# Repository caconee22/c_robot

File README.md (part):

<div align="center">

# 🤖 C_ROBOT

### 2026 IRC 씨름 로봇 — 자율주행 스모 로봇 V2

**카메라로 상대를 찾고, 네 모서리 컬러 센서로 경기장 홈을 피하며, 포크로 상대를 밀어내는 4.5kg급 자율 로봇**

[-gold?style=for-the-badge)](IRC2026_RETROSPECTIVE.md)

[개요](#-개요) ·
[하드웨어](#-하드웨어) ·
[시스템 구조](#-시스템-구조) ·
[경기 펌웨어](#-경기-펌웨어) ·
[시작하기](#-시작하기) ·
[타임라인](#-타임라인) ·
[대회 데이터](#-대회-데이터) ·
[배운 것](#-배운-것) ·
[문서](#-문서-지도)

</div>

---

## 🏆 결과

> **2026-11-13, 2026 IRC 씨름 로봇 대회 1위 — 1점 차 우승.**
>
> 첫 설계부터 우승까지 42일. 모터 드라이버와 메인 보드가 타고, 회로를 처음부터 다시 만들고,
> 대회 당일 경기 중에 ESP32가 멈추는 문제를 현장에서 고쳐 가며 얻은 결과다.
> 우승 펌웨어는 태그 [`irc2026-final`](https://github.com/caconee22/c_robot/tree/irc2026-final)에 그대로 남아 있다.

| | |
|---|---|
| 📅 **기간** | 2026-10-03 → 2026-11-13 (42일), 정리 11/14 |
| 🧠 **제어** | ESP32-S3 단독 판단 · 루프 1~2ms · 모터 명령 80ms 만료 감시 |
| 👁️ **영상** | Raspberry Pi 5 + Camera Module 3 Wide · 720p 60fps · 좌표만 50Hz UART |
| 🎨 **바닥** | AS7341 스펙트럼 센서 ×4 · 12단계 교정 · 3/10/20mm 간격 변화 대응 |
| 📈 **기록** | 커밋 79 · PR 9 · 주행 로그 80개 · 분석 67판 61분 · AI 대화 27일 |

---

## 📖 개요

C_ROBOT은 **2026 IRC 씨름 로봇 대회**에 나간 자율주행 스모 로봇의 통합 저장소다.
펌웨어, 영상 처리, 회로·PCB, 기구, 팀 일정, 주행 로그, 그리고 개발 과정의 AI 대화까지 한곳에 있다.

경기 규칙의 핵심은 단순하다. 경기장 위에서 **상대 로봇(컬러 타워를 단)을 찾아 밀어내고**,
경기장 가장자리의 **빨강·파랑 홈에 빠지지 않는 것**이다. 사람이 조종하지 않는다.

```
     ┌─────────── 경기장 ───────────┐
     │  🔵 홈          🔴 가운데 원   │     👁️ 카메라  →  상대 컬러 타워 좌표
     │        🤖 ──▶  🎯 상대        │     🎨 바닥 센서 ×4 →  홈·원 색 판별
     │  🔵 홈                  🔵 홈 │     ⚙️ ESP32 →  찾기·정렬·돌진·포크·회피
     └──────────────────────────────┘
```

이 로봇의 설계 원칙 세 가지:

1. **판단과 안전은 ESP32 한 곳에서.** 라즈베리파이는 "타워가 화면 어디에 있나"만 보낸다. 라즈가 꺼져도 로봇은 멈추지 않고 바닥 회피와 안전 기능은 그대로 돈다.
2. **루프를 막지 않는다.** 센서 수광, I2C, UART, 로그를 모두 짧은 단계로 쪼개 메인 루프가 1~2ms마다 돈다. 명령이 80ms 안에 갱신되지 않으면 별도 태스크가 모터를 세운다.
3. **실물로 확인하지 않은 것은 확정하지 않는다.** PC 시험 18,000여 회 통과도 "실물 보증"으로 쓰지 않고, 모든 값에 실측 여부를 표시했다.

---

## 🔧 하드웨어

<div align="center">

<sub>연결 구성도. 버튼 역할은 11/11에 바뀌었다(아래 "안전 설계" 표).</sub>

</div>

| 구성 | 부품 | 비고 |
|---|---|---|
| 메인 제어기 | **YD-ESP32-S3** (ESP32-S3-WROOM-1) | 자체 설계 **V2 기판** 위. Wi-Fi·PSRAM·네이티브 USB는 쓰지 않음 |
| 영상 | **Raspberry Pi 5** + **Camera Module 3 Wide** | 720p 60fps, 셔터 1ms, HSV 검출 → UART1 115200bps |
| 바닥 센서 | **AS7341** 11채널 스펙트럼 ×4 | TCA9548A 먹스 채널 0~3, 자체 백색 LED, 네 모서리 |
| 자세 | **MPU6050** IMU | 뒤집힘 비상정지, 로그용 방향 추정 |
| 모터 드라이버 | **BTS7960** ×2 | 20kHz PWM, 모터당 EN 하나. 명령은 ±1000(천분율), 상한 1000 |
| 구동 | DC 기어드 모터 ×2 → **HTD5M 20T 벨트** → 실리콘 바퀴 ×4 | 휠베이스 129mm (180mm였던 이전 기체의 털림을 줄이려고) |
| 바퀴 | 식품용 실리콘(Shore A40) 주조 | 일회용 몰드, 65mm 예비 설계 |
| 전원 | 3S·4S LiPo (둘 다 자동 판정) | 라즈는 USB-C PD 모듈로 따로 |
| 프레임 | 6061 알루미늄 5T (JLCCNC 가공) + PLA·PETG 출력물 | 무게 4,150g 실측(11/4), 한도 4,545g |
| 입력 | SW1·SW2 버튼, 상태 LED(NeoPixel) | LED 10가지 상태 |

<details>
<summary><b>📐 V2 기판 (KiCad) 보기</b></summary>

<div align="center">

</div>

- 원본: [`PCBV2/`](PCBV2/) (KiCad), 펌웨어 핀의 원본은 [`ESP_MAIN/include/pins_v2.hpp`](ESP_MAIN/include/pins_v2.hpp)
- 커넥터·배선 지도: [`img/c_robot_wiring_connector_map.png`](img/c_robot_wiring_connector_map.png)
- 이전 V1 기판: [`PCB/`](PCB/) (구형 로봇 `yd_esp32_s3_v1_husky`용)

</details>

<details>
<summary><b>⚙️ 기구 설계 근거 (휠베이스, 벨트, 무게중심)</b></summary>

- 휠베이스 129mm: 제자리 회전 시 횡슬립이 180mm 대비 약 28% 줄어든다 (`π × 휠베이스`, 565 → 405mm).
- 벨트: 전륜-후륜 129mm 구간 360mm, 모터-전륜 79mm 구간 260mm, 아이들러로 장력.
- 무게중심 목표: 앞축 65~70%, 높이 약 60mm.
- 최종 기체 3D 모델: [`3D/`](3D/) (Fusion 360 `.f3z`, V6.2)
- 전체 기록: [`docs/DESIGN_20261010.md`](docs/DESIGN_20261010.md), 벨트 도면: [`mechanical/belt/`](mechanical/belt/), 무게중심 계산기: [`robot-cg-simulator.html`](robot-cg-simulator.html)

</details>

---

## 🧭 시스템 구조

```mermaid
flowchart TB
    subgraph PI["🍓 Raspberry Pi 5"]
        CAM["Camera Module 3 Wide<br/>720p · 60fps · 셔터 1ms"] --> DET["tower_detector_hsv.py<br/>HSV · 모양 · ROI"]
        DET --> TX["pi_vision_sender.py<br/>14바이트 패킷 · 50Hz"]
        RX["esp_log_receiver.py<br/>run_*.csv · boots.csv"]
    end

    subgraph ESP["⚙️ ESP32-S3 (V2 기판)"]
        LINK["RaspberryLink<br/>헤더·범위·순번·신선도 120ms"]
        SENS["SensorManager<br/>AS7341 ×4 · 3회 확인"]
        IMU["IMU · TiltGuard"]
        SAFE["SystemManager<br/>버튼 · 고장 · 비상정지"]
        FSM["AlignFsm<br/>회피 › 포크 › 돌진 › 정렬 › 탐색"]
        DRV["DriveLogic → MotorController<br/>상한 1000 · 직진 보정 · 80ms 만료"]
        WD["만료 감시 태스크 5ms<br/>+ 태스크 워치독 1s"]
        LOG["RunLog · ResetReport"]
    end

    TX -- "UART1 115200<br/>타워 좌표" --> LINK
    LOG -- "UART1 TX<br/>상태·판단·리셋 원인" --> RX
    LINK --> FSM
    SENS --> FSM
    IMU --> SAFE
    SAFE --> FSM
    FSM --> DRV
    WD -. 명령 끊기면 브레이크 .-> DRV
    DRV --> BTS["BTS7960 ×2 → 모터 → 벨트 → 바퀴"]
```

**메인 루프 한 바퀴 (약 1~2ms)** — [`ESP_MAIN/src/main.cpp`](ESP_MAIN/src/main.cpp)

```text
① 안전 확인        ② 라즈 좌표 (최대 128바이트)   ③ 바닥 색 (짧은 I2C 단계)
④ 배터리·IMU       ⑤ 안전 재확인 (의도된 반복)    ⑥ FSM 판단
⑦ 좌우 출력 계산   ⑧ 모터 (80ms 기한)             ⑨ LED·로그 (가장 낮은 우선순위)
```

라즈 통신은 **CRC를 일부러 쓰지 않는다.** 짧은 고정 배선이라 헤더·버전·길이·상태 비트·좌표 범위·sequence·신선도 검사로 충분하다고 판단했다.

---

## 🎯 경기 펌웨어

최종 경기 FSM은 대회 사흘 전(11/10) 실물 로그를 보고 **기능 하나씩 붙여 가며 다시 짠** `AlignFsm`이다
([`ESP_MAIN/include/control/align_fsm.hpp`](ESP_MAIN/include/control/align_fsm.hpp)).
매 루프 위에서부터 처음 해당하는 하나를 고른다.

```mermaid
flowchart TD
    A{"모터 허용?"} -- 아니오 --> BR["🛑 브레이크"]
    A -- 예 --> B{"네 모서리 중<br/>빨강·파랑?"}
    B -- 예 --> ESC["↩️ 바닥 회피<br/>먼저 밟은 쪽 기준 · 락온 유지"]
    ESC --> CB{"빨강 + 먼 타워?"}
    CB -- 예 --> CIR["⭕ 가운데 원 돌아가기"]
    B -- 아니오 --> C{"타워가 가깝고<br/>가운데?"}
    C -- 예 --> FORK["🍴 포크 공격<br/>급제동 → 삽입 → 급가속 800"]
    C -- 아니오 --> D{"타워가 가운데<br/>(새 프레임 확인)?"}
    D -- 예 --> CH["🚀 돌진 800 + 조향"]
    D -- 아니오 --> E{"타워가 보임?"}
    E -- 예 --> AL["🎯 제자리 정렬<br/>멀수록 빠르게"]
    E -- 아니오 --> SR["🔍 마지막 본 쪽으로 회전 탐색"]
```

| 기동 | 무엇을 하나 | 우승 펌웨어 값 |
|---|---|---|
| 🔍 탐색 | 마지막으로 본 쪽으로 제자리 회전 | 출력 500 |
| 🎯 정렬 | 화면 중심과의 오차에 비례해 제자리 회전 | 350~450 |
| 🚀 돌진 | 새 프레임으로 중앙 확인 뒤 조향하며 전진 | 800 (조향 ±150) |
| 🍴 포크 공격 | 가까이서 급제동 → 포크를 상대 아래로 → 급가속 | 800 / 삽입 480 |
| ↩️ 바닥 회피 | 먼저 위험색을 밟은 모서리 기준으로 빠짐. 밀려서 들어가면 더 세게 | 650 / 밀려 들어감 750 |
| ⭕ 원 돌아가기 | 가운데 빨간 원 + 먼 타워면 물러나 돌아서 호를 그림 | 후진 600 → 회전 400 → 호 450 |
| ▶️ 시작 루틴 | 왼쪽 45° → 직진 2초 → 왼쪽 90° | **대회 마지막 날 끔** |

- 모든 숫자의 원본: [`control_config.hpp`](ESP_MAIN/include/control/control_config.hpp)와 각 모듈 헤더의 `config::` 블록
- 노랑은 단차일 뿐이라 피하지 않는다. 판정이 애매한 색(Unknown)에서는 추가 기동을 하지 않는다.
- 이전 FSM(`RobotFsm`: 탐색·확인·정렬·접근·돌진·브레이크·삽입·밀기·무작위 순회)은 코드에 남아 있고 `ALIGN_ONLY_FSM=false`로 되돌릴 수 있다.

### 🎨 바닥 색 판별

추가 가림막 없이 **기체 하부 그늘 + 센서 자체 백색 LED**로 바닥을 본다. 경기장 홈에는 10mm 단차가 있어서
센서-바닥 간격이 **3mm(밀착) · 10mm(평평) · 20~25mm(턱에 걸침)** 로 계속 변한다.

- 수광 약 5ms, 게인 X16, LED 20mA로 시작해 실물에서 조정했다. 같은 색이 3번 나와야 확정한다.
- 유색은 **채널 비율**로, 검정은 **밝기**도 함께 본다. 근접 포화, 떠 있을 때 유색을 검정으로 읽는 문제, 색 경계 혼합을 늘 고려했다.
- **12단계 교정:** 빨강·파랑·검정(노랑은 따로 앞뒤 두 번) × 평평 10mm·들림 20mm·눌림 3mm. 칩마다 NVS에 저장한다.

### 🛡️ 안전 설계

| 입력 | 동작 |
|---|---|
| 정지 중 SW1 또는 SW2 | 출발 |
| 구동 중 아무 버튼 0.5초 | **비상정지** (EN 차단, 구동 금지 래치) |
| 비상정지 중 두 버튼 동시 0.5초 | 소프트 리셋: 래치 해제, FSM을 처음 상태로 → 출발 대기 (11/11 전에는 재부팅해야 풀렸다) |
| 전원 켤 때 두 버튼 1초 | 벤치·색 교정 모드로 부팅 |
| IMU 80° 넘게 1초 | 비상정지 (뒤집힘, 11/10에 3초 → 1초) |
| 모터 명령 80ms 무갱신 | 감시 태스크(5ms)가 브레이크 |
| 메인 루프 멈춤 | 태스크 워치독 1초 → 리셋 → 리셋 원인을 라즈 `boots.csv`에 기록 |

> [!WARNING]
> 우승 펌웨어는 대회용으로 **워치독 리셋이 나면 버튼 없이 바로 다시 달린다**(비상정지 상태였다면 제외).
> 시연·보관 중에는 메인 전원을 끄거나, [`reset_report.hpp`](ESP_MAIN/include/system/reset_report.hpp)의
> `RESUME_AFTER_WATCHDOG`를 `false`로 바꿔 올린다.

> [!CAUTION]
> V2 기판은 EN·PWM 선에 풀다운이 없어서 ESP32가 리셋·부팅·정지된 순간 BTS7960 입력이 떠 모터가 혼자 돌 수 있다.
> 펌웨어로 막을 수 없는 구간이다. 바퀴를 띄우고, 비상정지를 손 닿는 곳에 두고 시험한다.

---

## 🚀 시작하기

### 필요한 것

- [PlatformIO](https://platformio.org/) (espressif32 6.11.0, Arduino core 2.0.17)
- Python 3.10+ (벤치 GUI, 로그 분석, 라즈 쪽 시험)
- 라즈베리파이 쪽: Raspberry Pi OS 64-bit, Picamera2, OpenCV — 새 SD 카드는 [`PI_RECOVERY.md`](PI_RECOVERY.md)

### 빌드·업로드

```bash
git clone https://github.com/caconee22/c_robot.git
cd c_robot/ESP_MAIN
git checkout irc2026-final                       # 우승 펌웨어 그대로 쓰려면
pio run -e yd_esp32_s3_v2 -t upload              # 경기용 (+ 부팅 때 두 버튼 → 벤치)
pio device monitor -b 57600                      # UART0 로그
```

| 환경 | 용도 |
|---|---|
| `yd_esp32_s3_v2` | **경기용** (V2 기판). 전원 켤 때 두 버튼 1초 → 벤치·교정 모드 |
| `robot_bench_v2_manual` | 벤치 전용: 저출력(40%) 시험, 진단, 12단계 색 교정 |
| `yd_esp32_s3_v1_husky` / `robot_bench_v1_husky` | 구형 로봇: V1 기판, TCS34725, HuskyLens(UART), 4S 고정 |
| `i2c_scanner_v2`, `raw_motor_v2` | 진단용. `raw_motor_v2`는 **안전 기능 없이 자동 구동** |

### 색 교정 (벤치 GUI)

```bash
python ESP_MAIN/tools/bench_gui.py     # Windows: ESP_MAIN/tools/run_bench_gui.cmd
```

"색 교정" 탭에서 12단계 안내를 따라간다 (카운트다운·측정 각 1초). 교정값은 NVS에 남아 경기용과 함께 쓴다.
**칩을 바꾸면 다시 교정해야 한다.** 원격 작업 때는 ESP32를 라즈 USB에 꽂고 `ESP_MAIN/tools/flash_from_pi.sh`로 올린다.

### 시험

```powershell
cd ESP_MAIN
powershell -ExecutionPolicy Bypass -File tests/run_host_tests.ps1 -V2     # 경기용 회귀 시험
powershell -ExecutionPolicy Bypass -File tests/run_host_tests.ps1 -Bench  # 벤치
python -m unittest discover -s ../tests -v                                # 라즈 쪽 (패킷·검출기·Wi-Fi 복구)
```

PC 시험은 실제 `setup()/loop()`와 생산 모듈을 가짜 GPIO·UART·I2C·NVS·시간에 연결해 돌린다.
전기적 브레이크, 실제 수광, 광학 성능은 이 시험으로 증명되지 않는다.

### 주행 로그 분석

```bash
python ESP_MAIN/tools/run_log_stats.py pi_backup/runs
```

상태별 시간, 회피 횟수·반복률, 원 우회 갇힘, 포크 성공률, 비정상 리셋을 표로 낸다.

---

## 🗂️ 저장소 구조

```text
c_robot/
├── ESP_MAIN/                  ⚙️ ESP32-S3 펌웨어 (PlatformIO)
│   ├── include/ src/          모듈별 헤더·구현 (control, sensors, motor, system, communication …)
│   ├── tests/host/            PC 회귀 시험 (가짜 하드웨어)
│   ├── tools/                 벤치 GUI, 라즈 경유 업로드, 로그 분석
│   └── archive/               10/31에 은퇴한 환경 (빌드 안 됨)
├── scripts/                   🍓 라즈: 검출기, 송신, 설정 앱, 로그 수신, systemd 서비스
├── tests/                     라즈 쪽 파이썬 시험
├── pi_backup/                 라즈 설정 백업 + 대회 주행 로그 80개 (runs/)
├── 3D/                       🧊 Fusion 360 전체 기체 모델 (씨름 로봇 V6.2.f3z)
├── PCB/  PCBV2/               🔌 V1·V2 회로·PCB (KiCad)
├── mechanical/belt/           벨트 구동계 계산·DXF·STEP
├── fsm_sim/                   브라우저 2D FSM 시뮬레이터 (10/18)
├── cv_tests/                  영상 필터 비교 실험 (10/06)
├── schedule/                  📅 팀 일정 페이지 (일정, 인수인계, 규정 점검, 로봇 설명, 순서도)
├── conversation_logs/         💬 Claude Code 개발 대화 (날짜별, 개인정보 가림)
├── docs/                      📚 타임라인, 라즈 안내, 예전 설계·영상 기록, 이미지
├── videos/irc2026_match_day/  🎬 대회 당일(11/13) 경기 영상 6개 (Git LFS)
├── dataset/ img/ samples/     영상·사진 원본 (보존)
├── IRC2026_RETROSPECTIVE.md   🏆 대회 회고
├── PI_RECOVERY.md             라즈 SD 카드를 새로 만들 때
└── AGENTS.md  CLAUDE.md       사람과 AI가 같이 따르는 작업 규칙
```

---

## 📅 타임라인

```mermaid
timeline
    title 42일 — 설계에서 우승까지
    10/03–10/10 : 저장소·V1 펌웨어 : 영상 필터 비교 : 휠베이스 129mm 확정
    10/14–10/27 : Claude Code 인수·코드맵 : V2 기판 납땜 : FSM 시뮬레이터 : CNC 발주·도착
    10/28–11/04 : 기구 3.0kg : ⚡ 드라이버·메인보드 소손 : 회로 재제작 : 첫 전체 동작
    11/05–11/08 : HSV 타워 검출·설정 앱 : 경기 FSM v1 : 3D 출력·실리콘 바퀴
    11/09–11/12 : 첫 실물 주행 : FSM 재구성·포크 공격 : 실행 로그 : 경기장 ROI
    11/13 : ⚠ 경기 중 ESP 정지 → 현장 수리 : 워치독 자동 재개 : 🏆 1위
```

| 날짜 | 무슨 일 |
|---|---|
| **10/05** | V1 펌웨어 구현, AS7341 연속 측정, 센서 간격 3/10/20mm 조건 정리 |
| **10/10** | 기구 설계 확정: 휠베이스 129mm, HTD5M 벨트, 6061 5T |
| **10/14** | Codex → Claude Code 인수, AI용 코드맵(`MAP.md`)과 헤더 계약 |
| **10/17** | V2 기판 SMD 납땜 |
| **10/20** | JLCCNC 가공 발주 |
| **10/25** | V2 기판 첫 전원 |
| **10/30** | 기구 조립 완료 3.0kg |
| **10/31** | ⚡ 모터 선이 바퀴에 끼어 드라이버 소손, 프린터 고장 |
| **11/01** | ⚡ 메인 보드 소손 → 11/2–3 회로 전부 재제작 |
| **11/04** | ✅ 첫 전체 동작, 12단계 색 교정, 라즈 → ESP32 50Hz 오류 0 |
| **11/05** | 타워 설정 앱, 경기 FSM에 벤치 결과 반영 |
| **11/08** | 무작위 순회·뒤집힘 정지·센서 재시도, 3D 출력 완료 |
| **11/09** | 🚗 경기 펌웨어 첫 실물 주행 |
| **11/10** | 🔁 경기 FSM 재구성 (`AlignFsm`), 포크 공격, 원 돌아가기, 실행 로그 |
| **11/11** | 두 버튼 규칙, 벤치·경기 펌웨어 통합, 노랑 교정 |
| **11/12** | 출력 800·상한 1000, 경기장 현장 시험, 카메라 ROI |
| **11/13** | 🏆 **대회 1위** — 경기 중 ESP 정지를 리셋 보고·워치독 재개로 버팀 |
| **11/14** | 태그 `irc2026-final`, 회고, 로그·대화 기록 보존 |

👉 **날짜·시각별 전체 기록: [`docs/TIMELINE.md`](docs/TIMELINE.md)**

---

## 📊 대회 데이터

11/10–11/13 주행 로그 중 10초 이상인 **67판, 61분**을 분석했다 ([회고](IRC2026_RETROSPECTIVE.md) §3).

```mermaid
pie showData
    title 상태별 주행 시간 비율 (%)
    "돌진" : 26
    "회피" : 18.5
    "정렬" : 17
    "탐색" : 16
    "원 돌아가기" : 12
    "포크" : 6
    "시작 루틴" : 5
```

| 지표 | 값 | 읽는 법 |
|---|---|---|
| 회피 | 1,089번 (분당 17.9번) | **79%가 직전 회피 2초 안에 다시 회피** — 같은 홈 앞에서 반복 |
| 회피 색 | 파랑 79% · 빨강 21% | 먼저 닿은 쪽: 앞왼 52% · 앞오 36% · 뒤 8% |
| 원 돌아가기 | 258번, 중앙값 1.3초 | 10초 넘게 갇힘 4번 (최대 29.1초) |
| 포크 공격 | 327번 → 삽입 73% → **밀기 61%** | 급제동 직후 회피로 끊긴 것 27% |
| 탐색 | 한 번에 중앙값 0.3초 | 영상 추적은 안정적 |
| 비정상 리셋 | 10번 (태스크 워치독 5, 인터럽트 워치독 5) | 모두 11/13. core dump 비어 있음 — 전원 쪽 추정, 미확정 |

원본: [`pi_backup/runs/`](pi_backup/runs/) (주행 80개 + `boots.csv`)

🎬 대회 당일 경기 영상: [`videos/irc2026_match_day/`](videos/irc2026_match_day/) (11/13 10:33–16:37, 6개, 약 0.65GB, Git LFS)

---

## 💡 배운 것

<table>
<tr>
<td width="50%" valign="top">

**🔌 하드웨어**

- **EN·PWM 선에 풀다운을.** ESP가 멈춘 순간 모터가 혼자 돈다.
- **모터 전원과 로직 5V를 분리하고** 큰 커패시터를. AMS1117은 5.1V 입력에서 여유 0.5V뿐.
- **배선은 움직이는 부품에서 떼어 고정.** 10/31 합선의 원인.
- 라즈 전원은 GPIO 5V 벅이 아니라 **USB-C PD**로. 부팅 부하에서 꺼졌다.
- 센서 커넥터와 3.3V 공급 점검. 부팅 때 센서 초기화 실패가 잦았다.
- 연습용 현수막과 **실제 경기장 턱은 다르다.** 센서가 25mm까지 떴다.

</td>
<td width="50%" valign="top">

**💻 소프트웨어**

- **로그부터.** 11/10 ESP32 → 라즈 실행 로그를 넣은 뒤로 튜닝 속도가 바뀌었다.
- 복잡해진 FSM은 **처음부터 한 기능씩** 다시 쌓는 게 빨랐다.
- 시간 기반 기동(회전 각도)은 **배터리 전압**에 따라 15% 넘게 달라진다.
- 회피 반복·원 갇힘처럼 **반복 횟수 제한이 없는 루프**가 판을 먹는다.
- 리셋 원인을 **다음 부팅에 보고**하게 해 두면 현장에서 원인을 좁힐 수 있다.
- 교정값은 칩을 바꾸면 사라진다 → PC로 내보내기·불러오기가 필요.

</td>
</tr>
</table>

**🤝 팀·과정**

- 같이 실물을 볼 수 있는 날이 손에 꼽혔다(11/2–4, 11/9–13). 그래서 원격으로 할 수 있는 것(설계 파일, 펌웨어, PC 시험, 결정)은 전부 미리 하고,
  현장 날은 실물 확인과 튜닝에만 썼다. 일정 페이지([`schedule/`](schedule/))가 그 조율 도구였다.
- 코딩을 모르는 현장 팀원이 AI와 함께 펌웨어를 고칠 수 있게 [`TEAM_GUIDE.md`](ESP_MAIN/TEAM_GUIDE.md)와 헤더 계약을 따로 썼다.
- 범위 축소를 기본값으로: "위험구역 회피 + 탐색 + 밀기"를 먼저, 나머지는 시간이 남을 때만.

---

## 🧑‍💻 AI와 함께 개발하기

이 프로젝트의 코드 대부분은 **Claude Code**(10/14부터, 그 전에는 Codex)와 대화하며 썼다. 그래서 저장소에 AI용 장치가 있다.

| 장치 | 역할 |
|---|---|
| [`AGENTS.md`](AGENTS.md), [`ESP_MAIN/AGENTS.md`](ESP_MAIN/AGENTS.md) | 사람과 AI가 같이 따르는 규칙: 안전 코드 보존, 핀 고정, 논블로킹, Wi-Fi·PSRAM·USB 금지, CRC를 쓰지 않는 이유 |
| [`ESP_MAIN/MAP.md`](ESP_MAIN/MAP.md) + 헤더 `// Contract` | 파일을 다 읽지 않고도 구조를 알게 하는 지도 (읽기 비용 절감) |
| [`ESP_MAIN/TEAM_GUIDE.md`](ESP_MAIN/TEAM_GUIDE.md) | 코딩 모르는 팀원이 AI에게 맡길 때의 쉬운 안내 |
| [`conversation_logs/`](conversation_logs/) | 27일치 실제 개발 대화 (사용자 메시지 약 700개, 개인정보 가림) |
| [`schedule/`](schedule/) | AI가 대화 중 나온 일정을 바로 반영한 팀 페이지 |

AI가 만든 결과도 **PC 시험 → 벤치(바퀴 띄움) → 실물** 순서로 확인했고, 실물에서 확인하지 않은 것은 문서에 "미확인"으로 남겼다.

---

## 📚 문서 지도

| 알고 싶은 것 | 문서 |
|---|---|
| 대회 결과, 최종 값, 로그 분석, 교훈 | [`IRC2026_RETROSPECTIVE.md`](IRC2026_RETROSPECTIVE.md) |
| 날짜·시각별 전체 기록 | [`docs/TIMELINE.md`](docs/TIMELINE.md) |
| 펌웨어 구조와 작업별로 열 파일 | [`ESP_MAIN/MAP.md`](ESP_MAIN/MAP.md) |
| 펌웨어 동작·센서·교정·통신 상세 | [`ESP_MAIN/README.md`](ESP_MAIN/README.md) |
| 실물 벤치 시험 절차 | [`ESP_MAIN/BENCH_TESTS.md`](ESP_MAIN/BENCH_TESTS.md) |
| 라즈 서비스·아이콘·파일 | [`docs/RASPBERRY_PI.md`](docs/RASPBERRY_PI.md) |
| 라즈 SD 카드 새로 만들기 | [`PI_RECOVERY.md`](PI_RECOVERY.md) |
| 10/10 기구 설계·기동 전략 기록 | [`docs/DESIGN_20261010.md`](docs/DESIGN_20261010.md) |
| 10월 초 영상 검출기(4필터) | [`docs/LEGACY_VISION.md`](docs/LEGACY_VISION.md), [`COLOR_DETECTOR.md`](COLOR_DETECTOR.md) |
| 대회 규정 원본 | [`2026년 IRC 씨름 로봇 규정-20260511.pdf`](2026년%20IRC%20씨름%20로봇%20규정-20260511.pdf) |

---

## 🛣️ 다음에 한다면

대회 뒤 기체는 다른 팀원에게 넘어갔다. 다음 기체·다음 대회를 위한 과제는 [회고 §5·§6](IRC2026_RETROSPECTIVE.md#5-다음-기판기체-교훈-하드웨어)에 있다.

- [ ] V3 기판: EN·PWM 풀다운, 전원 분리, 커패시터 보강
- [ ] 원 돌아가기 반복 제한, 같은 모서리 반복 회피 때 돌진 각도 바꾸기
- [ ] 워치독 재개 때 IMU 수평 기준 다시 배우기, 워치독 시간 재검토
- [ ] 교정값 PC 내보내기·불러오기
- [ ] 주행 로그에 바닥 센서 원값과 루프 최대 시간 추가

## 🚫 하지 않기로 한 것

- 통신 규격 변경, CRC·ACK 추가 (고정 배선, 의도된 설계)
- ESP32 Wi-Fi·OTA·PSRAM·네이티브 USB (V2는 ADC2·USB 핀을 측정에 씀)
- 추가 가림막·조리개·거리센서 같은 새 기구물이나 센서
- 안전 구조 재작성, 같은 하드웨어 버전 안에서 핀 변경
- 자동 재부팅·무한 재접속 같은 범용 자동 복구 (센서 채널 3회 재시도, 대회용 워치독 재개만 예외)

---

## 👥 팀

| | 역할 |
|---|---|
| **학현** | 소프트웨어 전반(펌웨어·영상·도구), 회로·V2 기판, 기구 설계, 일정 |
| **큰놈이** | 부품 조달, 3D 출력, 조립·배선, 현장 시험 |
| **예찬** | 하드웨어 시험 코드 |

함께 만든 도구: Claude Code (Anthropic), Codex (OpenAI).

## 📄 라이선스

라이선스를 따로 정하지 않았다. 코드와 자료를 쓰고 싶다면 저장소 소유자에게 먼저 연락한다.

<div align="center">

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
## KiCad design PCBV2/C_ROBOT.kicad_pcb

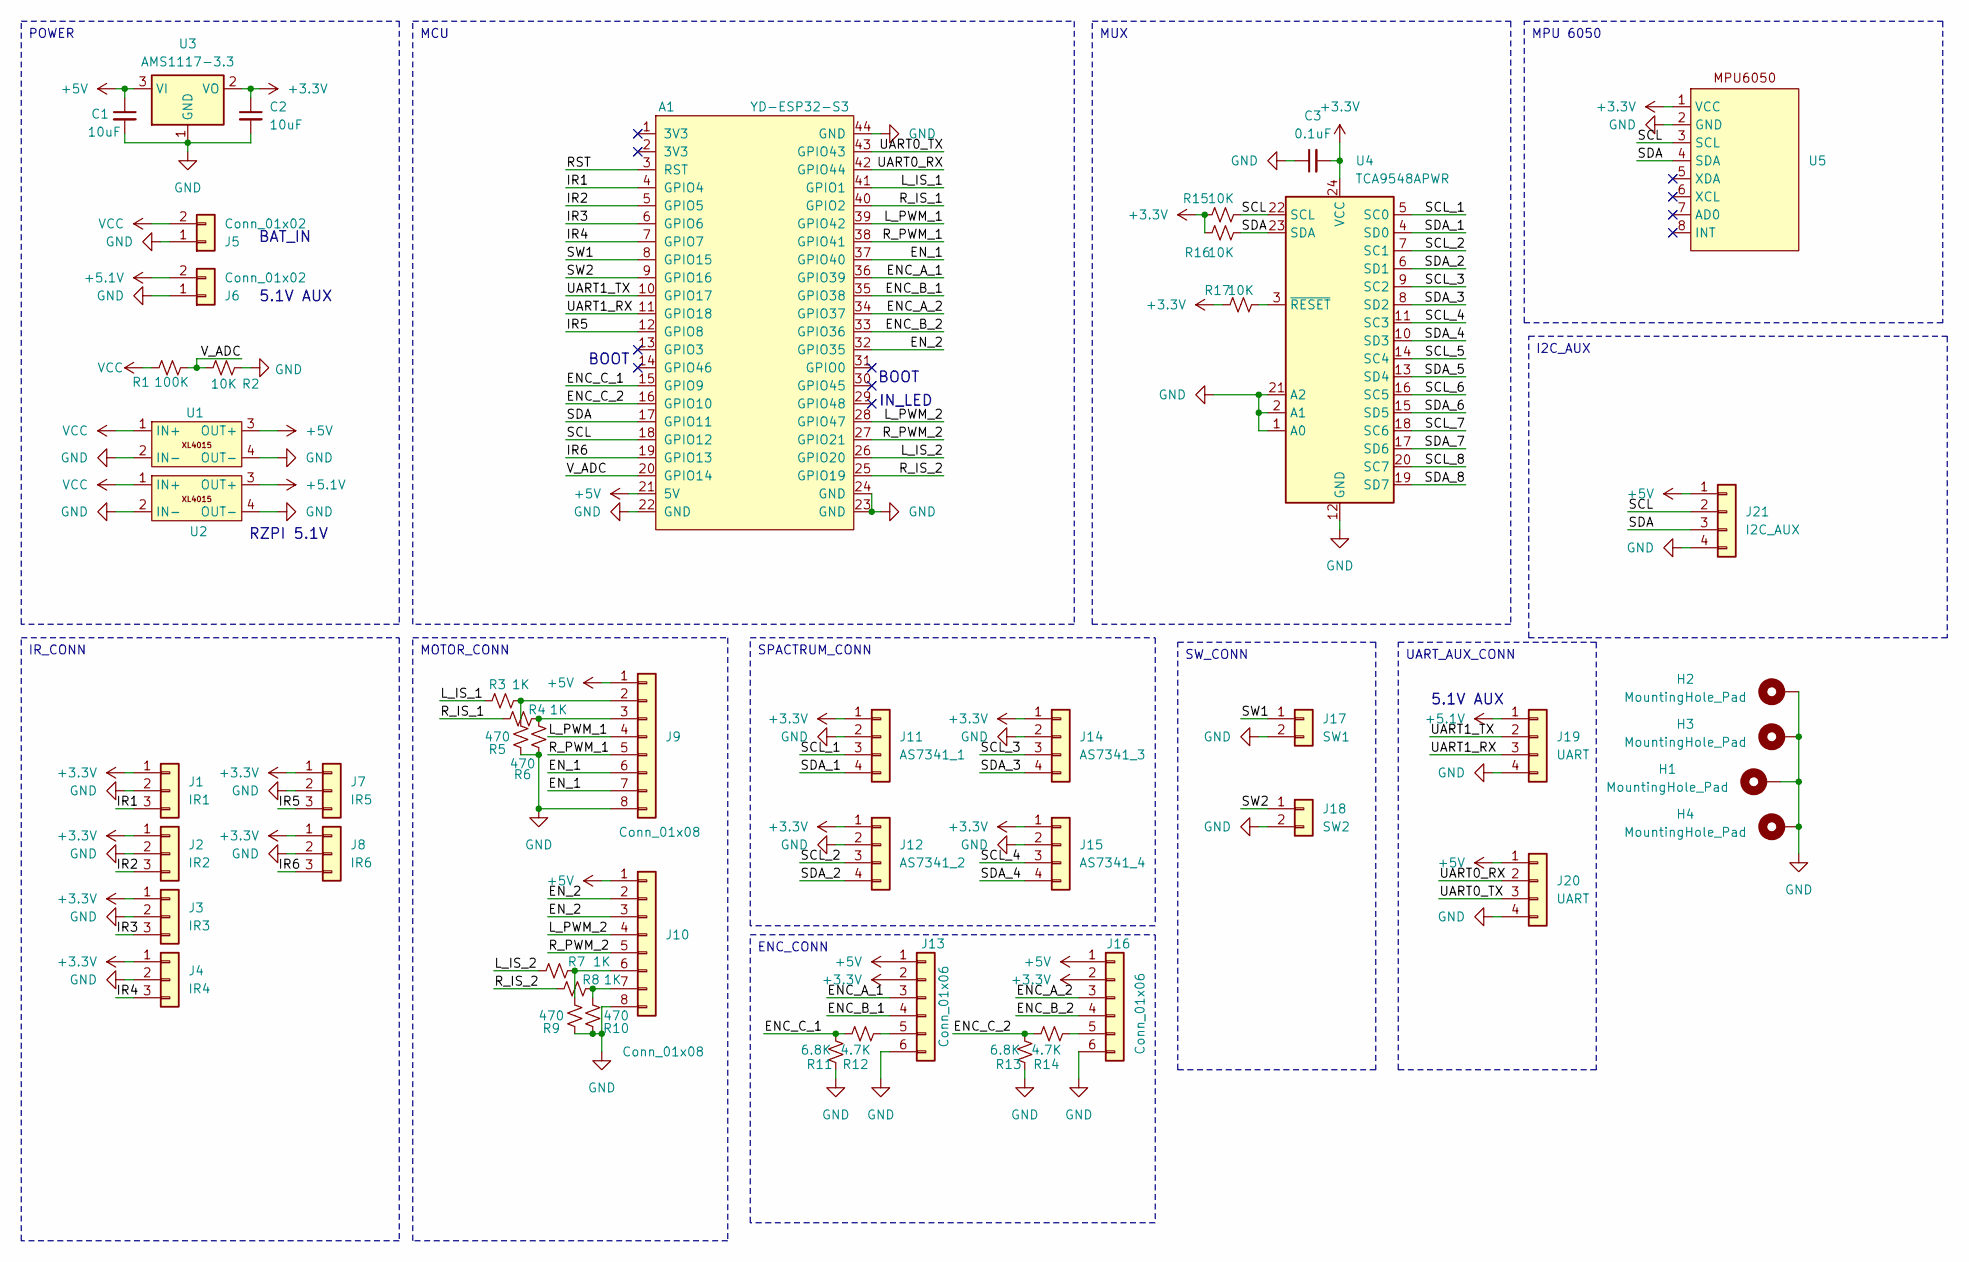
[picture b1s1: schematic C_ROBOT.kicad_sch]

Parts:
A1: YD-ESP32-S3
C1, C2: 10uF; C_0805_2012Metric_Pad1.18x1.45mm_HandSolder
C3: 0.1uF; C_0805_2012Metric_Pad1.18x1.45mm_HandSolder
H1, H2, H3, H4: MountingHole_Pad; MountingHole_3.2mm_M3_DIN965_Pad
J1: IR1; Molex_SPOX_5267-03A_1x03_P2.50mm_Vertical
J2: IR2; Molex_SPOX_5267-03A_1x03_P2.50mm_Vertical
J3: IR3; Molex_SPOX_5267-03A_1x03_P2.50mm_Vertical
J4: IR4; Molex_SPOX_5267-03A_1x03_P2.50mm_Vertical
J5: Conn_01x02; AMASS_XT30U-M_1x02_P5.0mm_Vertical
J6: Conn_01x02; Molex_SPOX_5267-02A_1x02_P2.50mm_Vertical
J7: IR5; Molex_SPOX_5267-03A_1x03_P2.50mm_Vertical
J8: IR6; Molex_SPOX_5267-03A_1x03_P2.50mm_Vertical
J9, J10: Conn_01x08; Molex_SPOX_5267-08A_1x08_P2.50mm_Vertical
J11: AS7341_1; Molex_SPOX_5267-04A_1x04_P2.50mm_Vertical
J12: AS7341_2; Molex_SPOX_5267-04A_1x04_P2.50mm_Vertical
J13, J16: Conn_01x06; Molex_SPOX_5267-06A_1x06_P2.50mm_Vertical
J14: AS7341_3; Molex_SPOX_5267-04A_1x04_P2.50mm_Vertical
J15: AS7341_4; Molex_SPOX_5267-04A_1x04_P2.50mm_Vertical
J17: SW1; Molex_SPOX_5267-02A_1x02_P2.50mm_Vertical
J18: SW2; Molex_SPOX_5267-02A_1x02_P2.50mm_Vertical
J19, J20: UART; Molex_SPOX_5267-04A_1x04_P2.50mm_Vertical
J21: I2C_AUX; Molex_SPOX_5267-04A_1x04_P2.50mm_Vertical
R1: 100K; R_0603_1608Metric
R2, R15, R16, R17: 10K; R_0603_1608Metric
R3, R4, R7, R8: 1K; R_0603_1608Metric
R5, R6, R9, R10: 470; R_0603_1608Metric
R11, R13: 6.8K; R_0603_1608Metric
R12, R14: 4.7K; R_0603_1608Metric
U1, U2: XL4015
U3: AMS1117-3.3; SOT-223-3_TabPin2
U4: TCA9548APWR; TSSOP-24_4.4x7.8mm_P0.65mm
U5: MPU6050

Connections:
+3.3V: C2.1, C3.2, J1.1, J2.1, J3.1, J4.1, J7.1, J8.1, J11.1, J12.1, J13.2, J14.1, J15.1, J16.2, R15.1, R16.1, R17.1, U3.2 (VO), U4.24 (VCC), U5.1 (VCC)
+5.1V: J6.2, J19.1, U2.3 (OUT+)
+5V: A1.21 (5V), C1.1, J9.1, J10.1, J13.1, J16.1, J20.1, J21.1, U1.3 (OUT+), U3.3 (VI)
/ENC_A_1: A1.36 (GPIO39), J13.3
/ENC_A_2: A1.34 (GPIO37), J16.3
/ENC_B_1: A1.35 (GPIO38), J13.4
/ENC_B_2: A1.33 (GPIO36), J16.4
/ENC_C_1: A1.15 (GPIO9), R11.2, R12.2
/ENC_C_2: A1.16 (GPIO10), R13.2, R14.2
/EN_1: A1.37 (GPIO40), J9.6, J9.7
/EN_2: A1.32 (GPIO35), J10.2, J10.3
/IR1: A1.4 (GPIO4), J1.3
/IR2: A1.5 (GPIO5), J2.3
/IR3: A1.6 (GPIO6), J3.3
/IR4: A1.7 (GPIO7), J4.3
/IR5: A1.12 (GPIO8), J7.3
/IR6: A1.19 (GPIO13), J8.3
/L_IS_1: A1.41 (GPIO1), R3.2
/L_IS_2: A1.26 (GPIO20), R7.2
/L_PWM_1: A1.39 (GPIO42), J9.4
/L_PWM_2: A1.28 (GPIO47), J10.4
/RST: A1.3 (RST)
/R_IS_1: A1.40 (GPIO2), R4.2
/R_IS_2: A1.25 (GPIO19), R8.2
/R_PWM_1: A1.38 (GPIO41), J9.5
/R_PWM_2: A1.27 (GPIO21), J10.5
/SCL: A1.18 (GPIO12), J21.2, R15.2, U4.22 (SCL), U5.3 (SCL)
/SCL_1: J11.3, U4.5 (SC0)
/SCL_2: J12.3, U4.7 (SC1)
/SCL_3: J14.3, U4.9 (SC2)
/SCL_4: J15.3, U4.11 (SC3)
/SCL_5: U4.14 (SC4)
/SCL_6: U4.16 (SC5)
/SCL_7: U4.18 (SC6)
/SCL_8: U4.20 (SC7)
/SDA: A1.17 (GPIO11), J21.3, R16.2, U4.23 (SDA), U5.4 (SDA)
/SDA_1: J11.4, U4.4 (SD0)
/SDA_2: J12.4, U4.6 (SD1)
/SDA_3: J14.4, U4.8 (SD2)
/SDA_4: J15.4, U4.10 (SD3)
/SDA_5: U4.13 (SD4)
/SDA_6: U4.15 (SD5)
/SDA_7: U4.17 (SD6)
/SDA_8: U4.19 (SD7)
/SW1: A1.8 (GPIO15), J17.1
/SW2: A1.9 (GPIO16), J18.1
/UART0_RX: A1.42 (GPIO44), J20.2
/UART0_TX: A1.43 (GPIO43), J20.3
/UART1_RX: A1.11 (GPIO18), J19.3
/UART1_TX: A1.10 (GPIO17), J19.2
/V_ADC: A1.20 (GPIO14), R1.1, R2.2
GND: A1.22 (GND), A1.23 (GND), A1.24 (GND), A1.44 (GND), C1.2, C2.2, C3.1, H1.1 (1_1), H2.1 (1_1), H3.1 (1_1), H4.1 (1_1), J1.2, J2.2, J3.2, J4.2, J5.1, J6.1, J7.2, J8.2, J9.8, J10.8, J11.2, J12.2, J13.6, J14.2, J15.2, J16.6, J17.2, J18.2, J19.4, J20.4, J21.4, R2.1, R5.1, R6.1, R9.1, R10.1, R11.1, R13.1, U1.2 (IN-), U1.4 (OUT-), U2.2 (IN-), U2.4 (OUT-), U3.1 (GND), U4.1 (A0), U4.2 (A1), U4.12 (GND), U4.21 (A2), U5.2 (GND)
unnamed: J9.2, R3.1, R5.2
unnamed: J9.3, R4.1, R6.2
unnamed: J10.6, R7.1, R9.2
unnamed: J10.7, R8.1, R10.2
unnamed: J13.5, R12.1
unnamed: J16.5, R14.1
unnamed: R17.2, U4.3 (~RESET)
VCC: J5.2, R1.2, U1.1 (IN+), U2.1 (IN+)

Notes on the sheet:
BAT_IN
BOOT
RZPI 5.1V
5.1V AUX
IN_LED
I2C_AUX
IR_CONN
MPU 6050
MOTOR_CONN
ENC_CONN
UART_AUX_CONN
MUX
MCU
POWER
SW_CONN
SPACTRUM_CONN

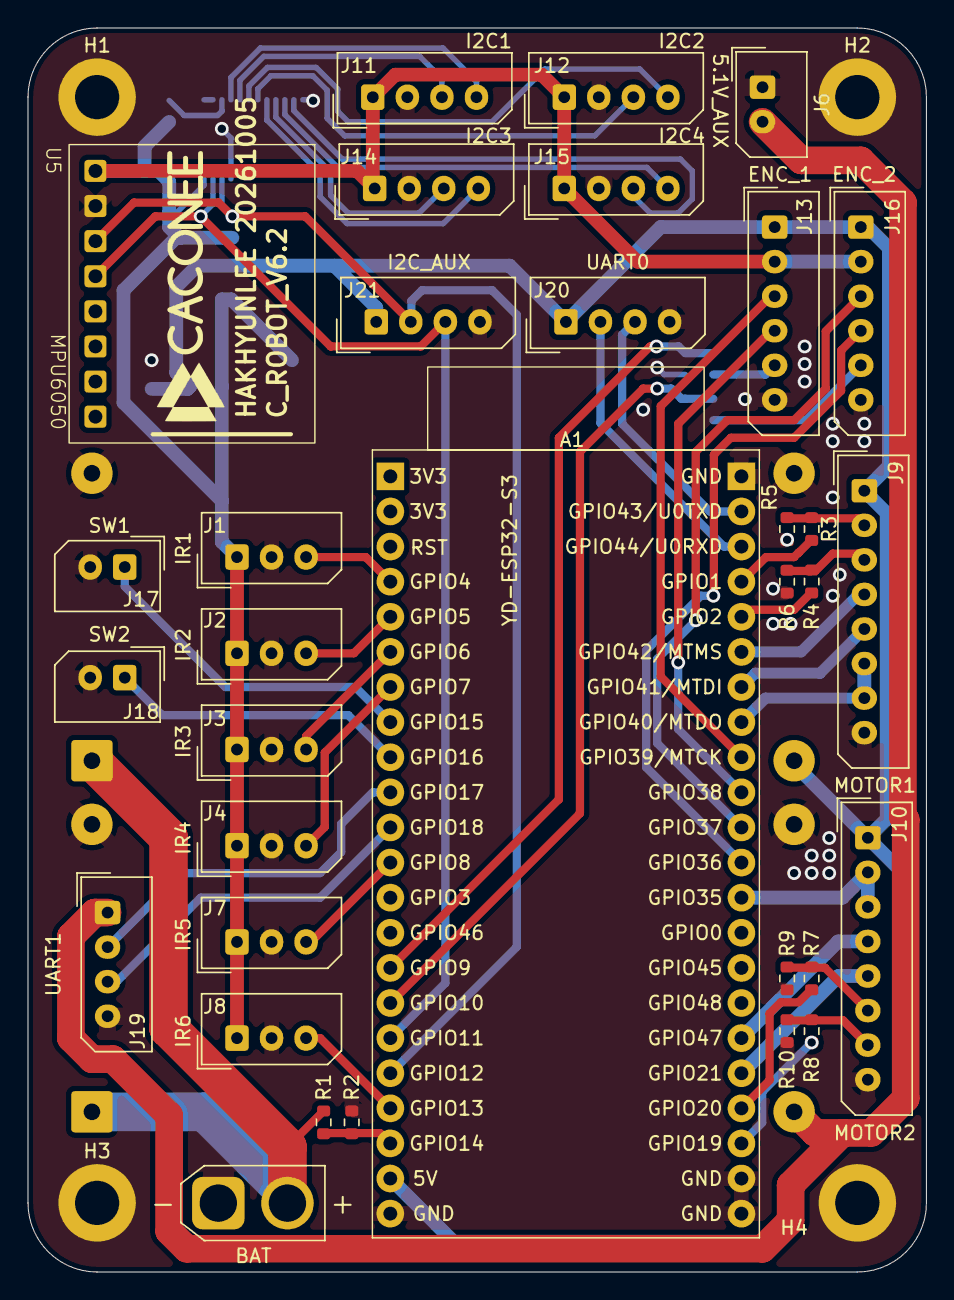
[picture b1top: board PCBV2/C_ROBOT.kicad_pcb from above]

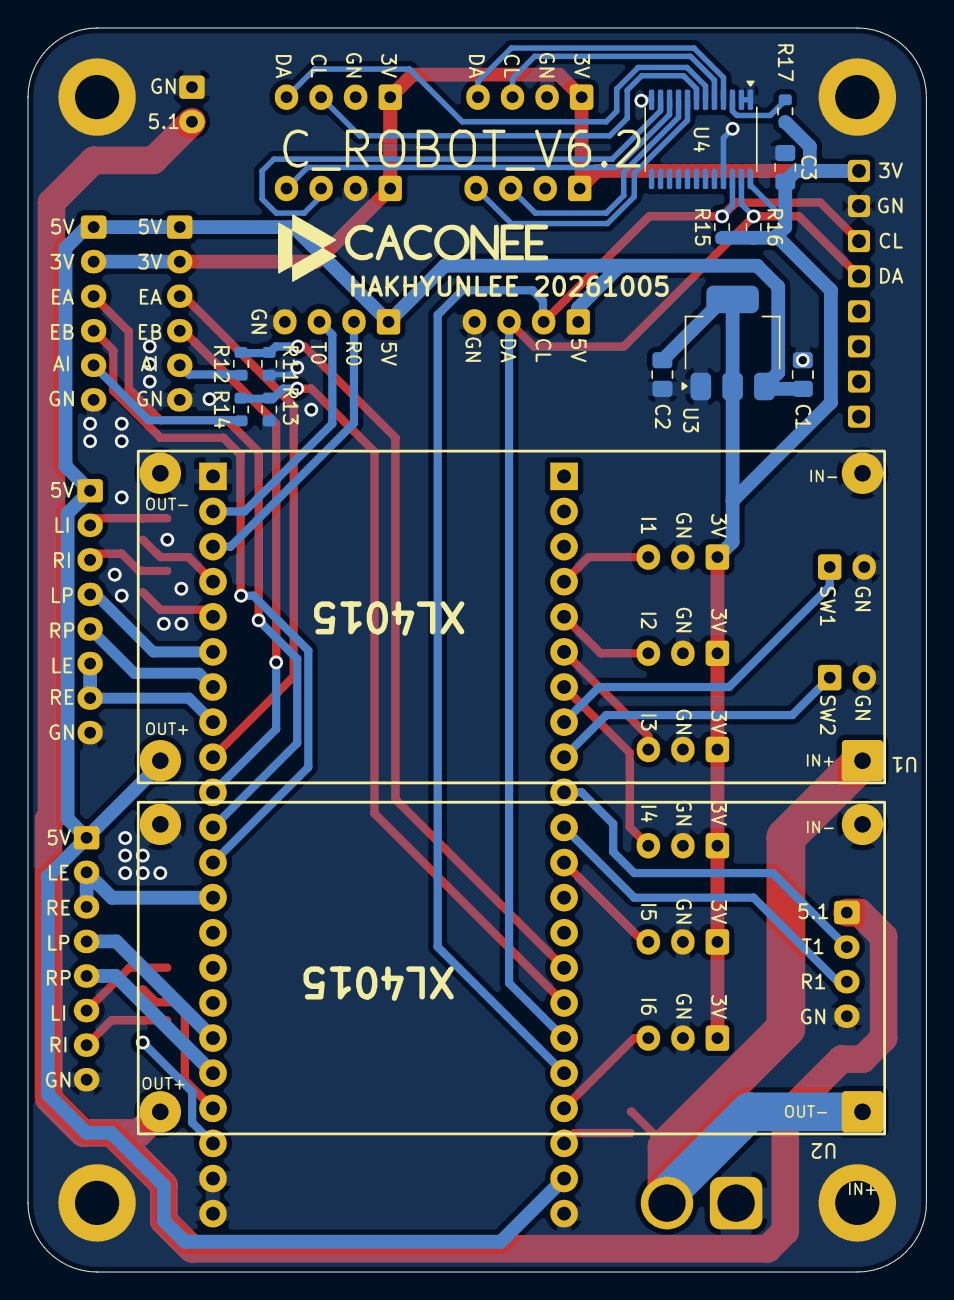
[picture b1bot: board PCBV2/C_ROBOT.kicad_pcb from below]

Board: 2 copper layers, 65.0 x 90.0 mm, 51 parts (14 on the bottom side), 51 nets.

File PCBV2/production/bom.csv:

Designator,Footprint,Quantity,Value,LCSC Part #
A1,YD-ESP32-S3,1,YD-ESP32-S3,
"C1, C2",0805,2,10uF,
C3,0805,1,0.1uF,
J1,Molex_SPOX_5267-03A_1x03_P2.50mm_Vertical,1,IR1,
"J10, J9",Molex_SPOX_5267-08A_1x08_P2.50mm_Vertical,2,Conn_01x08,
J11,Molex_SPOX_5267-04A_1x04_P2.50mm_Vertical,1,AS7341_1,
J12,Molex_SPOX_5267-04A_1x04_P2.50mm_Vertical,1,AS7341_2,
"J13, J16",Molex_SPOX_5267-06A_1x06_P2.50mm_Vertical,2,Conn_01x06,
J14,Molex_SPOX_5267-04A_1x04_P2.50mm_Vertical,1,AS7341_3,
J15,Molex_SPOX_5267-04A_1x04_P2.50mm_Vertical,1,AS7341_4,
J17,Molex_SPOX_5267-02A_1x02_P2.50mm_Vertical,1,SW1,
J18,Molex_SPOX_5267-02A_1x02_P2.50mm_Vertical,1,SW2,
"J19, J20, J21",Molex_SPOX_5267-04A_1x04_P2.50mm_Vertical,3,UART,
J2,Molex_SPOX_5267-03A_1x03_P2.50mm_Vertical,1,IR2,
J3,Molex_SPOX_5267-03A_1x03_P2.50mm_Vertical,1,IR3,
J4,Molex_SPOX_5267-03A_1x03_P2.50mm_Vertical,1,IR4,
J5,AMASS_XT30U-M_1x02_P5.0mm_Vertical,1,Conn_01x02,
J6,Molex_SPOX_5267-02A_1x02_P2.50mm_Vertical,1,Conn_01x02,
J7,Molex_SPOX_5267-03A_1x03_P2.50mm_Vertical,1,IR5,
J8,Molex_SPOX_5267-03A_1x03_P2.50mm_Vertical,1,IR6,
R1,0603,1,100K,
"R10, R5, R6, R9",0603,4,470,
"R11, R13",0603,2,6.8K,
"R12, R14",0603,2,4.7K,
"R15, R16, R17, R2",0603,4,10K,
"R3, R4, R7, R8",0603,4,1K,
"U1, U2",XL4015,2,~,
U3,SOT-223-3_TabPin2,1,AMS1117-3.3,
U4,TSSOP-24_4.4x7.8mm_P0.65mm,1,TCA9548APWR,
U5,MPU6050,1,~,

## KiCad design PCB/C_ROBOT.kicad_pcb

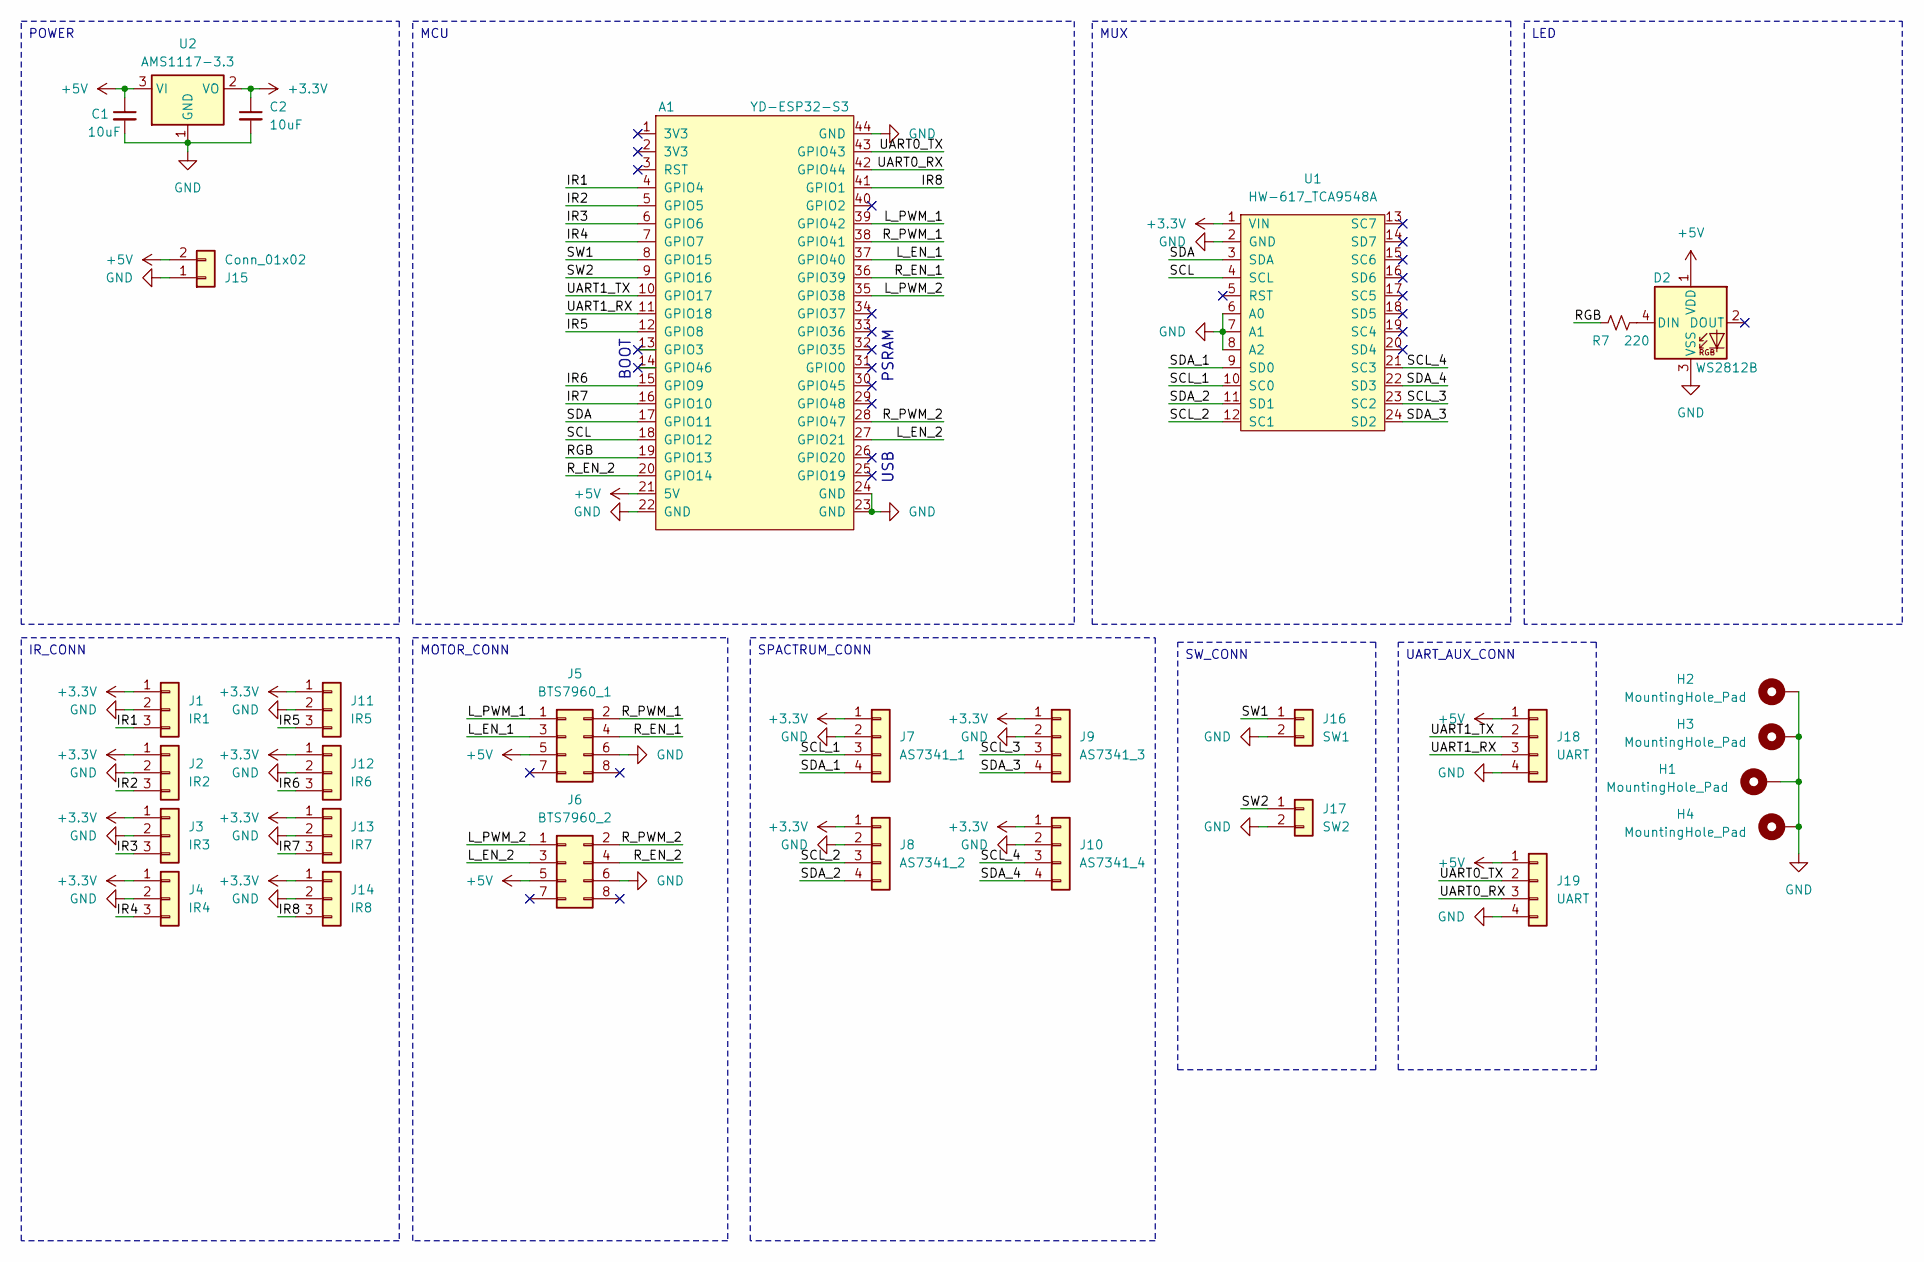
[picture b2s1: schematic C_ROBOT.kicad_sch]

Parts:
A1: YD-ESP32-S3
C1, C2: 10uF; C_0805_2012Metric_Pad1.18x1.45mm_HandSolder
D2: WS2812B; LED_WS2812B_PLCC4_5.0x5.0mm_P3.2mm
H1, H2, H3, H4: MountingHole_Pad; MountingHole_3.2mm_M3_DIN965_Pad
J1: IR1; Molex_SPOX_5267-03A_1x03_P2.50mm_Vertical
J2: IR2; Molex_SPOX_5267-03A_1x03_P2.50mm_Vertical
J3: IR3; Molex_SPOX_5267-03A_1x03_P2.50mm_Vertical
J4: IR4; Molex_SPOX_5267-03A_1x03_P2.50mm_Vertical
J5: BTS7960_1; Molex_SPOX_5267-06A_1x06_P2.50mm_Vertical
J6: BTS7960_2; Molex_SPOX_5267-06A_1x06_P2.50mm_Vertical
J7: AS7341_1; Molex_SPOX_5267-04A_1x04_P2.50mm_Vertical
J8: AS7341_2; Molex_SPOX_5267-04A_1x04_P2.50mm_Vertical
J9: AS7341_3; Molex_SPOX_5267-04A_1x04_P2.50mm_Vertical
J10: AS7341_4; Molex_SPOX_5267-04A_1x04_P2.50mm_Vertical
J11: IR5; Molex_SPOX_5267-03A_1x03_P2.50mm_Vertical
J12: IR6; Molex_SPOX_5267-03A_1x03_P2.50mm_Vertical
J13: IR7; Molex_SPOX_5267-03A_1x03_P2.50mm_Vertical
J14: IR8; Molex_SPOX_5267-03A_1x03_P2.50mm_Vertical
J15: Conn_01x02; AMASS_XT30U-M_1x02_P5.0mm_Vertical
J16: SW1; Molex_SPOX_5267-02A_1x02_P2.50mm_Vertical
J17: SW2; Molex_SPOX_5267-02A_1x02_P2.50mm_Vertical
J18, J19: UART; Molex_SPOX_5267-04A_1x04_P2.50mm_Vertical
R7: 220; R_0805_2012Metric_Pad1.20x1.40mm_HandSolder
U1: HW-617_TCA9548A; HW-617
U2: AMS1117-3.3; SOT-223-3_TabPin2

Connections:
+3.3V: C2.1, J1.1, J2.1, J3.1, J4.1, J7.1, J8.1, J9.1, J10.1, J11.1, J12.1, J13.1, J14.1, U1.1 (VIN), U2.2 (VO)
+5V: A1.21 (5V), C1.1, D2.1 (VDD), J5.5, J6.5, J15.2, J18.1, J19.1, U2.3 (VI)
/IR1: A1.4 (GPIO4), J1.3
/IR2: A1.5 (GPIO5), J2.3
/IR3: A1.6 (GPIO6), J3.3
/IR4: A1.7 (GPIO7), J4.3
/IR5: A1.12 (GPIO8), J11.3
/IR6: A1.15 (GPIO9), J12.3
/IR7: A1.16 (GPIO10), J13.3
/IR8: A1.41 (GPIO1), J14.3
/L_EN_1: A1.37 (GPIO40), J5.3
/L_EN_2: A1.27 (GPIO21), J6.3
/L_PWM_1: A1.39 (GPIO42), J5.1
/L_PWM_2: A1.35 (GPIO38), J6.1
/RGB: A1.19 (GPIO13), R7.2
/R_EN_1: A1.36 (GPIO39), J5.4
/R_EN_2: A1.20 (GPIO14), J6.4
/R_PWM_1: A1.38 (GPIO41), J5.2
/R_PWM_2: A1.28 (GPIO47), J6.2
/SCL: A1.18 (GPIO12), U1.4 (SCL)
/SCL_1: J7.3, U1.10 (SC0)
/SCL_2: J8.3, U1.12 (SC1)
/SCL_3: J9.3, U1.23 (SC2)
/SCL_4: J10.3, U1.21 (SC3)
/SDA: A1.17 (GPIO11), U1.3 (SDA)
/SDA_1: J7.4, U1.9 (SD0)
/SDA_2: J8.4, U1.11 (SD1)
/SDA_3: J9.4, U1.24 (SD2)
/SDA_4: J10.4, U1.22 (SD3)
/SW1: A1.8 (GPIO15), J16.1
/SW2: A1.9 (GPIO16), J17.1
/UART0_RX: A1.42 (GPIO44), J19.3
/UART0_TX: A1.43 (GPIO43), J19.2
/UART1_RX: A1.11 (GPIO18), J18.3
/UART1_TX: A1.10 (GPIO17), J18.2
GND: A1.22 (GND), A1.23 (GND), A1.24 (GND), A1.44 (GND), C1.2, C2.2, D2.3 (VSS), H1.1 (1_1), H2.1 (1_1), H3.1 (1_1), H4.1 (1_1), J1.2, J2.2, J3.2, J4.2, J5.6, J6.6, J7.2, J8.2, J9.2, J10.2, J11.2, J12.2, J13.2, J14.2, J15.1, J16.2, J17.2, J18.4, J19.4, U1.2 (GND), U1.6 (A0), U1.7 (A1), U1.8 (A2), U2.1 (GND)
unnamed: D2.4 (DIN), R7.1

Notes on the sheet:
BOOT
USB
PSRAM
IR_CONN
MOTOR_CONN
UART_AUX_CONN
MUX
MCU
POWER
SW_CONN
LED
SPACTRUM_CONN

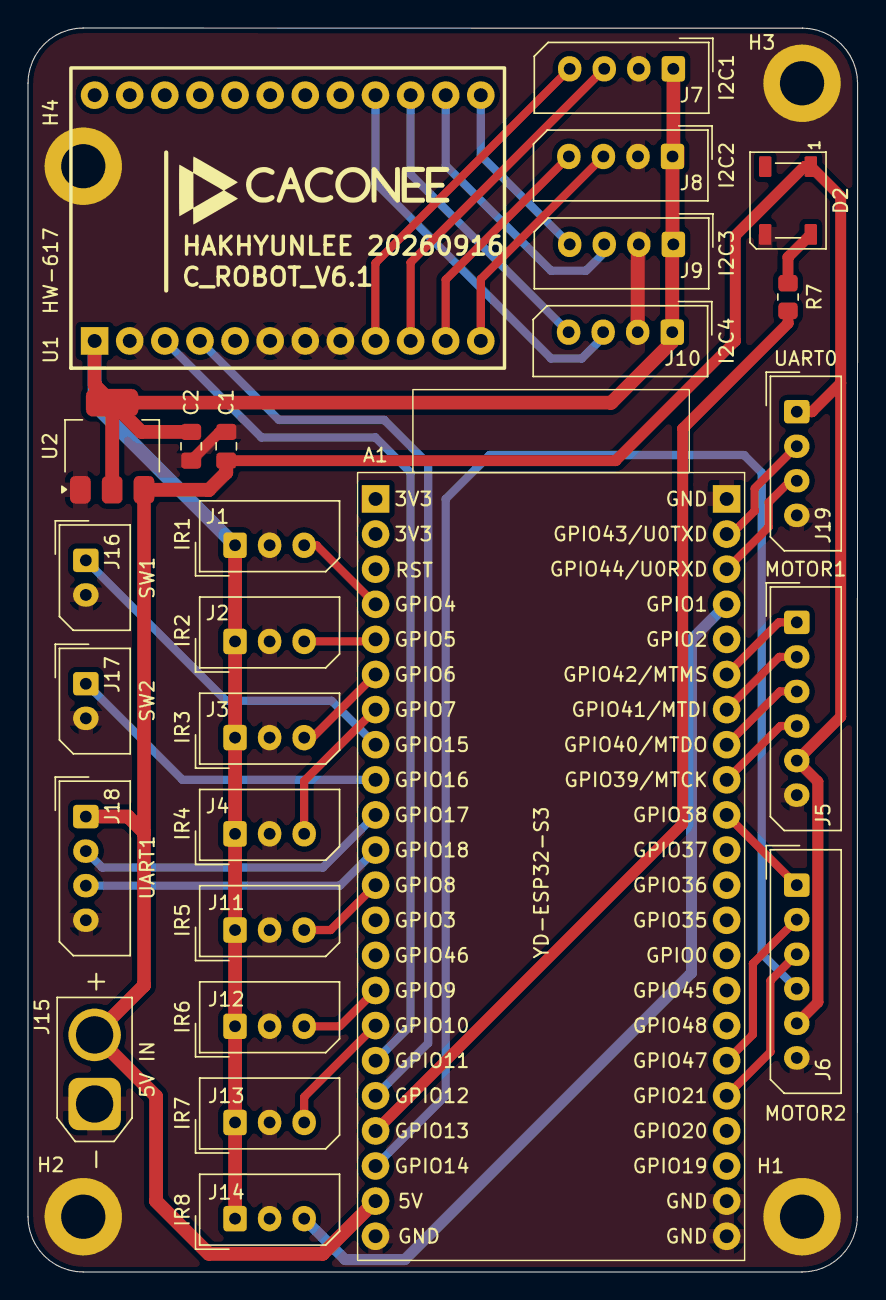
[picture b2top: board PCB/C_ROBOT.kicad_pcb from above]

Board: 2 copper layers, 60.0 x 90.0 mm, 30 parts (0 on the bottom side), 37 nets.

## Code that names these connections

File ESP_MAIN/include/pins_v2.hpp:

#pragma once

// V2 board pin map. Included only through pins.hpp when HW_VERSION == 2.
// Source: PCBV2/C_ROBOT.kicad_sch netlist, confirmed by the user 2026-10-14.
// Not yet verified on an assembled V2 board.
//
// Banned on this board (AGENTS.md): Wi-Fi, PSRAM/external flash, native USB.
// GPIO19/20 are the USB pins and are used here as motor current inputs.

#include <Arduino.h>

namespace pins {

// Switches use INPUT_PULLUP and are active LOW.
constexpr gpio_num_t SAFETY_SWITCH = GPIO_NUM_15;  // SW1
constexpr gpio_num_t START_SWITCH = GPIO_NUM_16;   // SW2

// Raspberry Pi communication.
constexpr gpio_num_t UART1_TX = GPIO_NUM_17;
constexpr gpio_num_t UART1_RX = GPIO_NUM_18;

// Main I2C bus: TCA9548A (spectral sensors on channels 0..3), MPU6050 IMU
// directly on the bus, and the auxiliary I2C connector J21.
constexpr gpio_num_t I2C_SDA = GPIO_NUM_11;
constexpr gpio_num_t I2C_SCL = GPIO_NUM_12;

// Status LED. V2 has only the on-board WS2812; GPIO13 is IR6 now.
constexpr gpio_num_t RGB_LED_INTERNAL = GPIO_NUM_48;
#define PINS_HAS_EXTERNAL_RGB_LED 0

// UART0 is shared by COM, SiK telemetry, and debug output.
constexpr gpio_num_t UART0_TX = GPIO_NUM_43;
constexpr gpio_num_t UART0_RX = GPIO_NUM_44;

// BTS7960 motor driver 1: left motor (J9). L_EN and R_EN share one pin.
constexpr gpio_num_t MOTOR1_LPWM = GPIO_NUM_42;
constexpr gpio_num_t MOTOR1_RPWM = GPIO_NUM_41;
constexpr gpio_num_t MOTOR1_EN = GPIO_NUM_40;

// BTS7960 motor driver 2: right motor (J10). L_EN and R_EN share one pin.
constexpr gpio_num_t MOTOR2_LPWM = GPIO_NUM_47;
constexpr gpio_num_t MOTOR2_RPWM = GPIO_NUM_21;
// GPIO35 is wired to the octal PSRAM inside N16R8/N8R8 modules. If the V2
// bench test shows EN_2 glitching at power-up or not following the command,
// jumper EN_2 to GPIO38 (or GPIO39) and change only this line:
//   constexpr gpio_num_t MOTOR2_EN = GPIO_NUM_38;
// The SW1 ISR EN mask is computed from this constant, so nothing else changes.
constexpr gpio_num_t MOTOR2_EN = GPIO_NUM_35;

// Existing code drives L_EN and R_EN separately; on V2 they are one wire.
constexpr gpio_num_t MOTOR1_LEN = MOTOR1_EN;
constexpr gpio_num_t MOTOR1_REN = MOTOR1_EN;
constexpr gpio_num_t MOTOR2_LEN = MOTOR2_EN;
constexpr gpio_num_t MOTOR2_REN = MOTOR2_EN;

// BTS7960 current sense (IS) through 1 kOhm, 470 Ohm to GND. Analog input.
// Use: wall push and stall detection only. GPIO19/20 are ADC2.
constexpr gpio_num_t MOTOR1_L_IS = GPIO_NUM_1;
constexpr gpio_num_t MOTOR1_R_IS = GPIO_NUM_2;
constexpr gpio_num_t MOTOR2_L_IS = GPIO_NUM_20;
constexpr gpio_num_t MOTOR2_R_IS = GPIO_NUM_19;

// Analog IR inputs IR1..IR6 (J1..J4, J7, J8). Purpose still to be confirmed.
// GPIO13 is ADC2.
constexpr gpio_num_t IR_INPUTS[6] = {GPIO_NUM_4, GPIO_NUM_5, GPIO_NUM_6,
                                     GPIO_NUM_7, GPIO_NUM_8, GPIO_NUM_13};

// Battery voltage through 100 kOhm / 10 kOhm (x11). GPIO14 is ADC2.
constexpr gpio_num_t BATTERY_ADC = GPIO_NUM_14;

// Encoders (J13 left, J16 right). Wired but NOT used: never configure these
// pins. GPIO36/37 are also octal PSRAM pins on R8 modules.
constexpr gpio_num_t ENCODER1_A = GPIO_NUM_39;
constexpr gpio_num_t ENCODER1_B = GPIO_NUM_38;
constexpr gpio_num_t ENCODER1_C = GPIO_NUM_9;   // Through 6.8k/4.7k divider.
constexpr gpio_num_t ENCODER2_A = GPIO_NUM_37;
constexpr gpio_num_t ENCODER2_B = GPIO_NUM_36;
constexpr gpio_num_t ENCODER2_C = GPIO_NUM_10;  // Through 6.8k/4.7k divider.

static_assert(MOTOR2_EN != GPIO_NUM_36 && MOTOR2_EN != GPIO_NUM_37,
              "GPIO36/37 are octal PSRAM pins; use GPIO38 or GPIO39");
static_assert(MOTOR1_EN != GPIO_NUM_19 && MOTOR1_EN != GPIO_NUM_20 &&
                  MOTOR2_EN != GPIO_NUM_19 && MOTOR2_EN != GPIO_NUM_20,
              "GPIO19/20 are current-sense inputs");
static_assert(MOTOR1_EN != MOTOR2_EN, "Each motor needs its own EN pin");

}  // namespace pins
